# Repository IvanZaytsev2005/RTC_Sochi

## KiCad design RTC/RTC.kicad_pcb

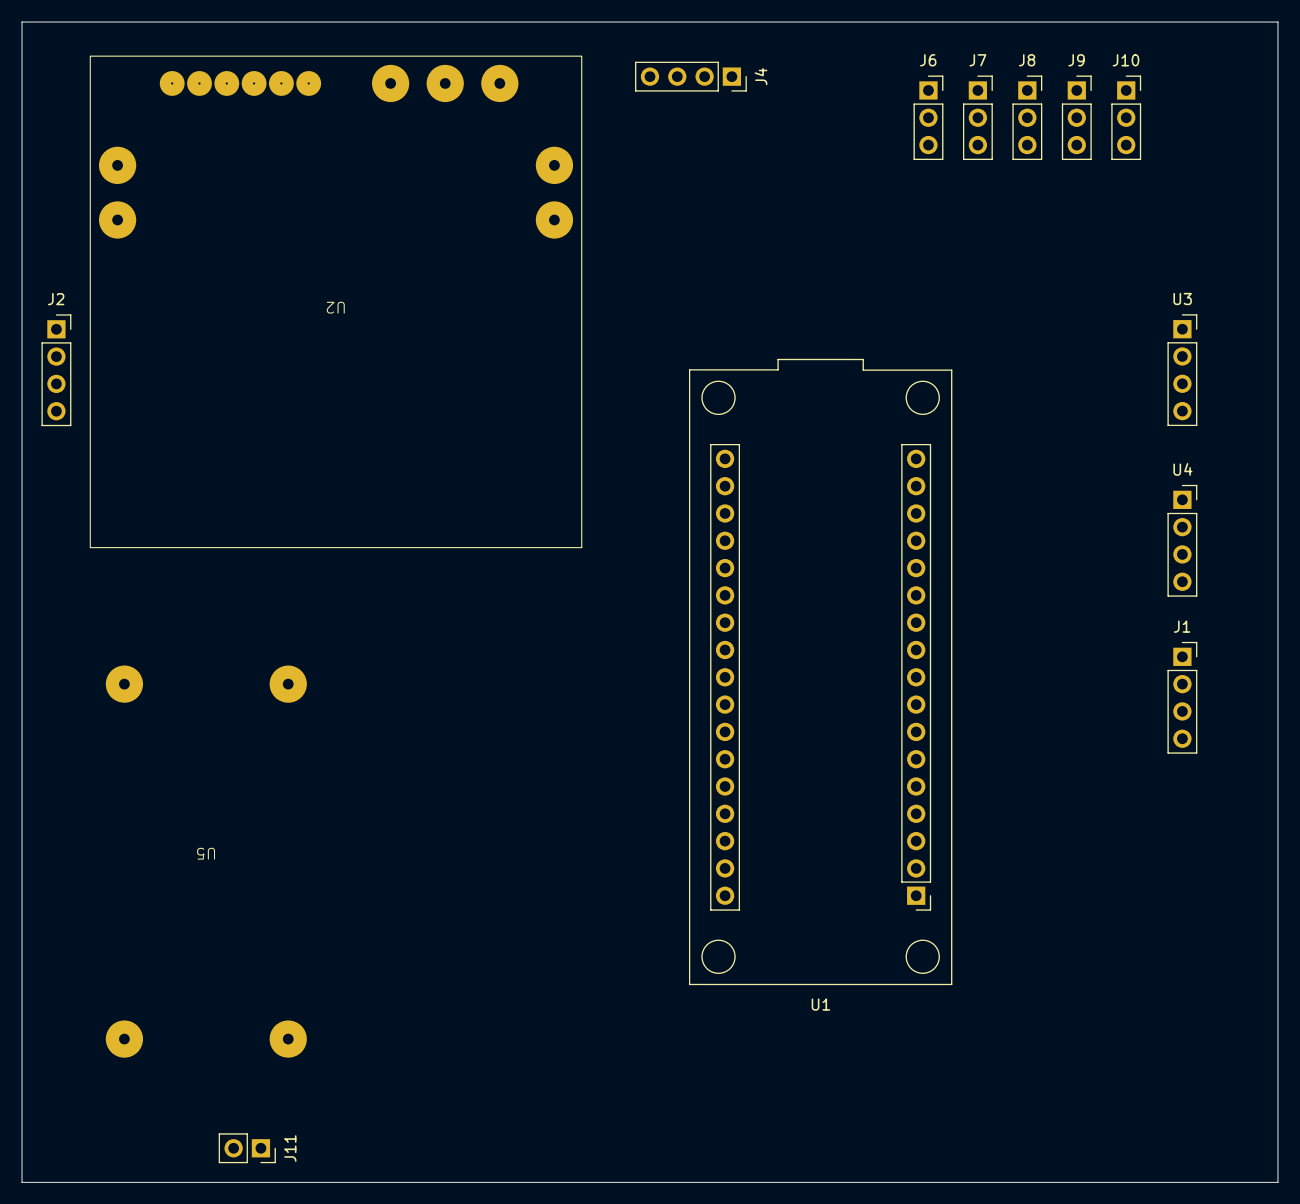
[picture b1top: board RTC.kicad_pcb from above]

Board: 2 copper layers, 116.8 x 108.0 mm, 14 parts (0 on the bottom side), 2 nets, no tracks yet.

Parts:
J1: Rasberry_to_stm; PinSocket_1x04_P2.54mm_Vertical
J2: Encoder R; PinSocket_1x04_P2.54mm_Vertical
J4: Encoder L; PinSocket_1x04_P2.54mm_Vertical
J6, J10: Servo1; PinSocket_1x03_P2.54mm_Vertical
J7: Servo2; PinSocket_1x03_P2.54mm_Vertical
J8: Servo3; PinSocket_1x03_P2.54mm_Vertical
J9: Servo4; PinSocket_1x03_P2.54mm_Vertical
J11: Power 12V; PinSocket_1x02_P2.54mm_Vertical
U1: YAAJ_BlackPill_2
U2: L298N; L298_Module
U3, U4: PinSocket_1x04_P2.54mm_Vertical
U5: UBEC_POWER

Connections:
/5v: J1.1, J2.1, J4.1, J6.2, J7.2, J8.2, J9.2, J10.2
GND: J1.4, J2.4, J4.4, J6.1, J7.1, J8.1, J9.1, J10.1, J11.2

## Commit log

2023-11-21 for 2 motors, 2 HC-SR04, 5 serv PWM, 2 encoders
2023-11-27 work all without Servo5 (rotation man)
2024-02-10 Work with PID on velocity
2024-04-11 Work So so
2024-11-22 commit 22.11.24
